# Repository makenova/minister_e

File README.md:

# Minister_E

Minister_e is a hot swap 40% with a centered USB port and the layout of the prime_e V2.
I made this because the designer of the prime_e had no intention of making a hot swap version of the V2 PCB and I wanted one.

The step file can be found in the [docs](./docs) folder.

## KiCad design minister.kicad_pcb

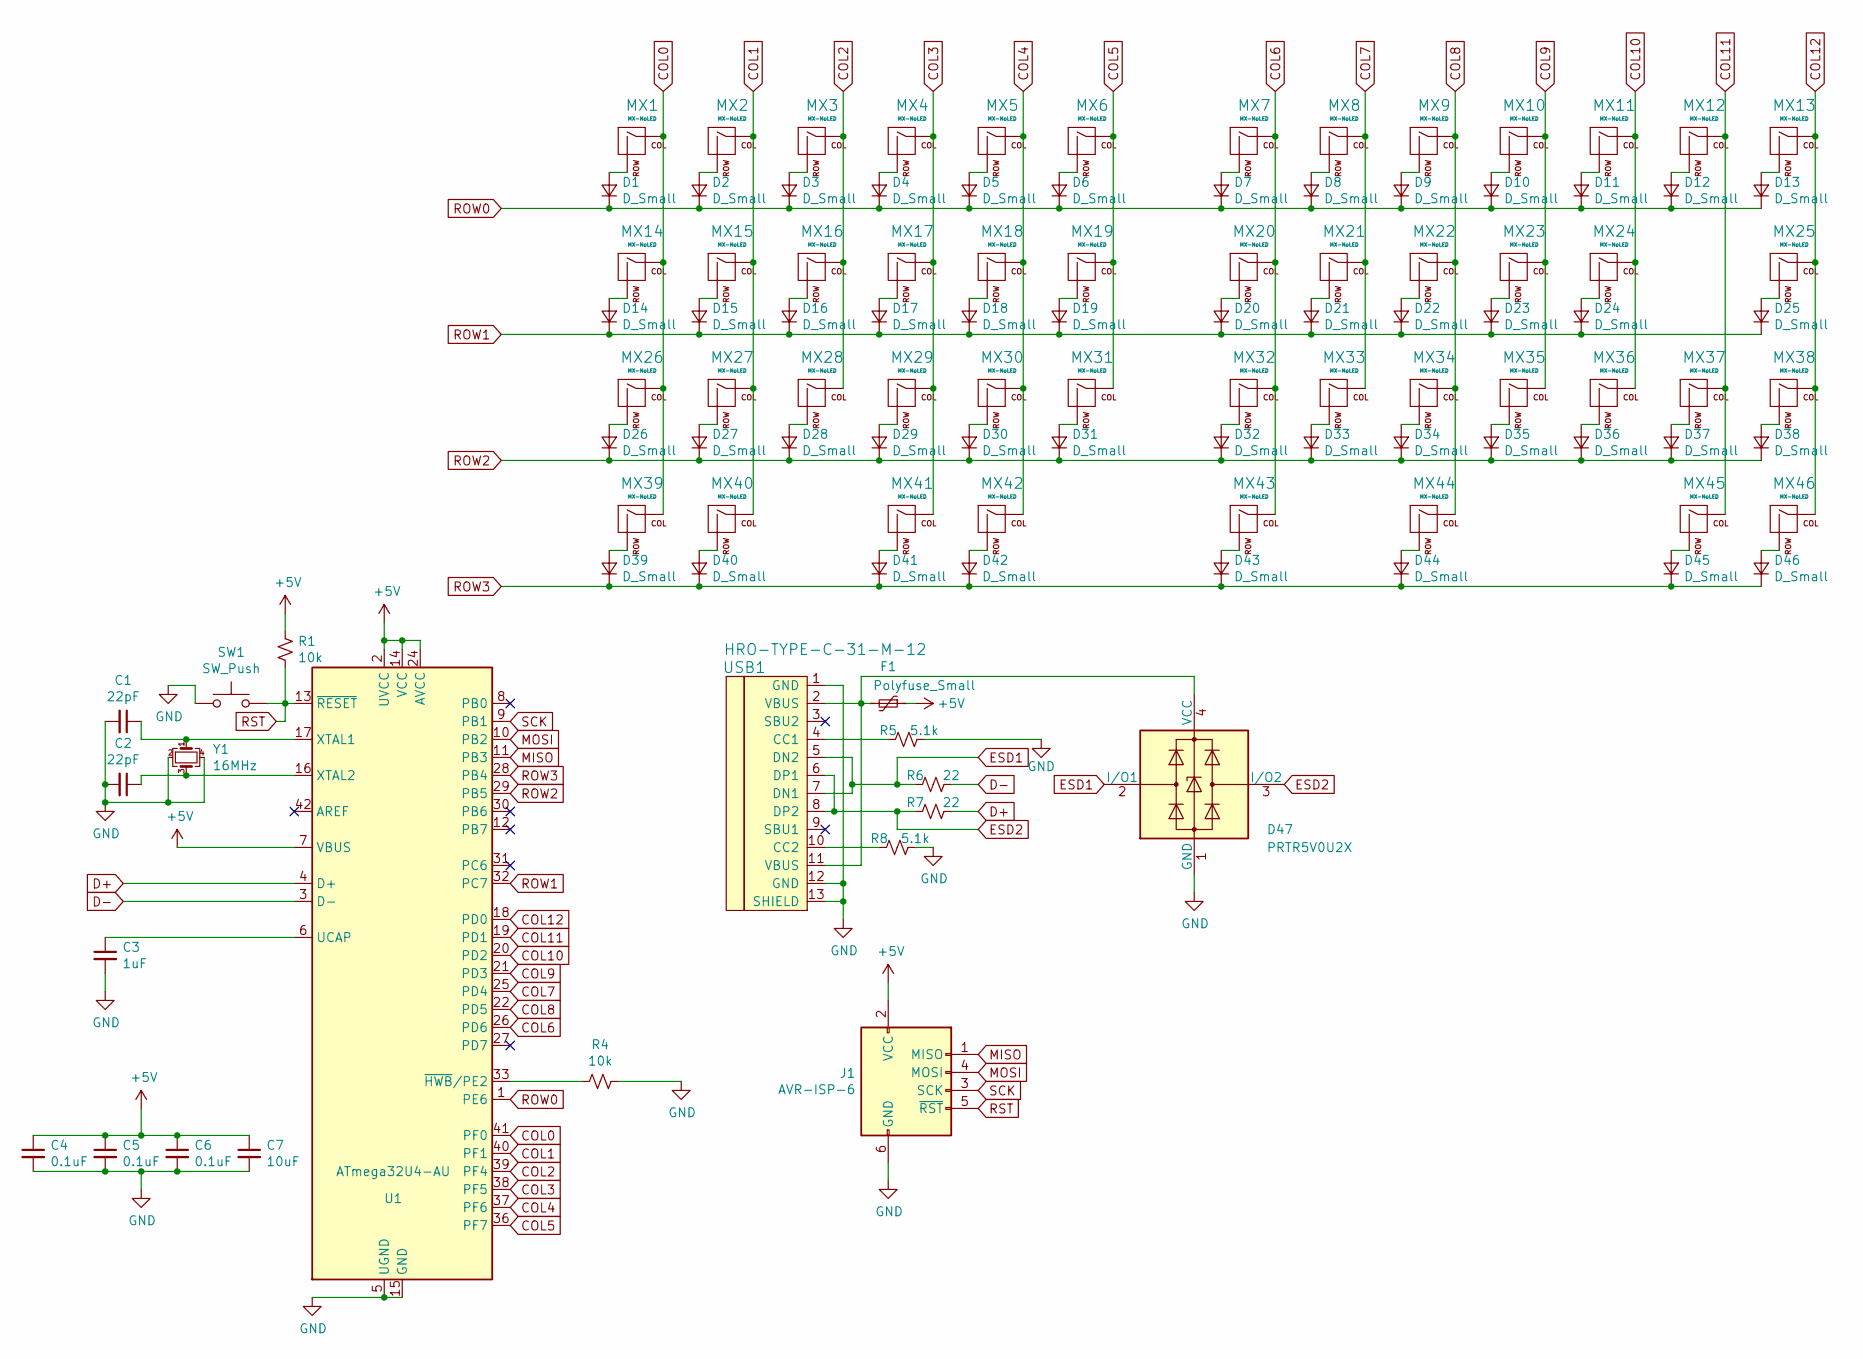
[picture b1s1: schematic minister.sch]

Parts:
C1, C2: 22pF; C_0805_2012Metric
C3: 1uF; C_0805_2012Metric
C4, C5, C6: 0.1uF; C_0805_2012Metric
C7: 10uF; C_0805_2012Metric
D1, D2, D3, D4, D5, D6, D7, D8, D9, D10, D11, D12, D13, D14, D15, D16, D17, D18, D19, D20, D21, D22, D23, D24, D25, D26, D27, D28, D29, D30, D31, D32, D33, D34, D35, D36, D37, D38, D39, D40, D41, D42, D43, D44, D45, D46: D_Small; D_SOD-123
D47: PRTR5V0U2X; SOT-143_Handsoldering
F1: Polyfuse_Small; Fuse_1206_3216Metric
J1: AVR-ISP-6; IDC-Header_2x03_P2.54mm_Vertical
MX1, MX2, MX3, MX4, MX5, MX6, MX7, MX8, MX9, MX10, MX11, MX12, MX13, MX15, MX16, MX17, MX18, MX19, MX20, MX21, MX22, MX23, MX24, MX27, MX28, MX29, MX30, MX31, MX32, MX33, MX34, MX35, MX36, MX37: MX-NoLED; MXOnly-1U-Hotswap
MX14, MX38, MX39, MX40, MX41, MX44, MX45, MX46: MX-NoLED; MXOnly-1.25U-Hotswap
MX25, MX26: MX-NoLED; MXOnly-1.75U-Hotswap
MX42: MX-NoLED; MXOnly-2U-Hotswap-ReversedStabilizers
MX43: MX-NoLED; MXOnly-2.25U-Hotswap-ReversedStabilizers
R1, R4: 10k; R_0805_2012Metric
R5, R8: 5.1k; R_0805_2012Metric
R6, R7: 22; R_0805_2012Metric
SW1: SW_Push; SKQG-1155865
U1: ATmega32U4-AU; TQFP-44_10x10mm_P0.8mm
USB1: HRO-TYPE-C-31-M-12; HRO-TYPE-C-31-M-12-HandSoldering
Y1: 16MHz; Crystal_SMD_3225-4Pin_3.2x2.5mm

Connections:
+5V: C4.1, C5.1, C6.1, C7.1, F1.1, J1.2 (VCC), R1.1, U1.2 (UVCC), U1.7 (VBUS), U1.14 (VCC), U1.24 (AVCC), U1.34 (VCC), U1.44 (AVCC)
COL0: MX1.1 (COL), MX14.1 (COL), MX26.1 (COL), MX39.1 (COL), U1.41 (PF0)
COL1: MX2.1 (COL), MX15.1 (COL), MX27.1 (COL), MX40.1 (COL), U1.40 (PF1)
COL2: MX3.1 (COL), MX16.1 (COL), MX28.1 (COL), U1.39 (PF4)
COL3: MX4.1 (COL), MX17.1 (COL), MX29.1 (COL), MX41.1 (COL), U1.38 (PF5)
COL4: MX5.1 (COL), MX18.1 (COL), MX30.1 (COL), MX42.1 (COL), U1.37 (PF6)
COL5: MX6.1 (COL), MX19.1 (COL), MX31.1 (COL), U1.36 (PF7)
COL6: MX7.1 (COL), MX20.1 (COL), MX32.1 (COL), MX43.1 (COL), U1.26 (PD6)
COL7: MX8.1 (COL), MX21.1 (COL), MX33.1 (COL), U1.25 (PD4)
COL8: MX9.1 (COL), MX22.1 (COL), MX34.1 (COL), MX44.1 (COL), U1.22 (PD5)
COL9: MX10.1 (COL), MX23.1 (COL), MX35.1 (COL), U1.21 (PD3)
COL10: MX11.1 (COL), MX24.1 (COL), MX36.1 (COL), U1.20 (PD2)
COL11: MX12.1 (COL), MX37.1 (COL), MX45.1 (COL), U1.19 (PD1)
COL12: MX13.1 (COL), MX25.1 (COL), MX38.1 (COL), MX46.1 (COL), U1.18 (PD0)
D+: R7.1, U1.4 (D+)
D-: R6.1, U1.3 (D-)
ESD1: D47.2 (I/O1), R6.2, USB1.5 (DN2), USB1.7 (DN1)
ESD2: D47.3 (I/O2), R7.2, USB1.6 (DP1), USB1.8 (DP2)
GND: C1.2, C2.2, C3.2, C4.2, C5.2, C6.2, C7.2, D47.1 (GND), J1.6 (GND), R4.1, R5.1, R8.1, SW1.1, U1.5 (UGND), U1.15 (GND), U1.23 (GND), U1.35 (GND), U1.43 (GND), USB1.1 (GND), USB1.12 (GND), USB1.13 (SHIELD), Y1.2, Y1.4
MISO: J1.1 (MISO), U1.11 (PB3)
MOSI: J1.4 (MOSI), U1.10 (PB2)
unnamed: C1.1, U1.17 (XTAL1), Y1.1
unnamed: C2.1, U1.16 (XTAL2), Y1.3
unnamed: C3.1, U1.6 (UCAP)
unnamed: D1.2 (A), MX1.2 (ROW)
unnamed: D2.2 (A), MX2.2 (ROW)
unnamed: D3.2 (A), MX3.2 (ROW)
unnamed: D4.2 (A), MX4.2 (ROW)
unnamed: D5.2 (A), MX5.2 (ROW)
unnamed: D6.2 (A), MX6.2 (ROW)
unnamed: D7.2 (A), MX7.2 (ROW)
unnamed: D8.2 (A), MX8.2 (ROW)
unnamed: D9.2 (A), MX9.2 (ROW)
unnamed: D10.2 (A), MX10.2 (ROW)
unnamed: D11.2 (A), MX11.2 (ROW)
unnamed: D12.2 (A), MX12.2 (ROW)
unnamed: D13.2 (A), MX13.2 (ROW)
unnamed: D14.2 (A), MX14.2 (ROW)
unnamed: D15.2 (A), MX15.2 (ROW)
unnamed: D16.2 (A), MX16.2 (ROW)
unnamed: D17.2 (A), MX17.2 (ROW)
unnamed: D18.2 (A), MX18.2 (ROW)
unnamed: D19.2 (A), MX19.2 (ROW)
unnamed: D20.2 (A), MX20.2 (ROW)
unnamed: D21.2 (A), MX21.2 (ROW)
unnamed: D22.2 (A), MX22.2 (ROW)
unnamed: D23.2 (A), MX23.2 (ROW)
unnamed: D24.2 (A), MX24.2 (ROW)
unnamed: D25.2 (A), MX25.2 (ROW)
unnamed: D26.2 (A), MX26.2 (ROW)
unnamed: D27.2 (A), MX27.2 (ROW)
unnamed: D28.2 (A), MX28.2 (ROW)
unnamed: D29.2 (A), MX29.2 (ROW)
unnamed: D30.2 (A), MX30.2 (ROW)
unnamed: D31.2 (A), MX31.2 (ROW)
unnamed: D32.2 (A), MX32.2 (ROW)
unnamed: D33.2 (A), MX33.2 (ROW)
unnamed: D34.2 (A), MX34.2 (ROW)
unnamed: D35.2 (A), MX35.2 (ROW)
unnamed: D36.2 (A), MX36.2 (ROW)
unnamed: D37.2 (A), MX37.2 (ROW)
unnamed: D38.2 (A), MX38.2 (ROW)
unnamed: D39.2 (A), MX39.2 (ROW)
unnamed: D40.2 (A), MX40.2 (ROW)
unnamed: D41.2 (A), MX41.2 (ROW)
unnamed: D42.2 (A), MX42.2 (ROW)
unnamed: D43.2 (A), MX43.2 (ROW)
unnamed: D44.2 (A), MX44.2 (ROW)
unnamed: D45.2 (A), MX45.2 (ROW)
unnamed: D46.2 (A), MX46.2 (ROW)
unnamed: D47.4 (VCC), F1.2, USB1.2 (VBUS), USB1.11 (VBUS)
unnamed: R4.2, U1.33 (~HWB~/PE2)
unnamed: R5.2, USB1.4 (CC1)
unnamed: R8.2, USB1.10 (CC2)
ROW0: D1.1 (K), D2.1 (K), D3.1 (K), D4.1 (K), D5.1 (K), D6.1 (K), D7.1 (K), D8.1 (K), D9.1 (K), D10.1 (K), D11.1 (K), D12.1 (K), D13.1 (K), U1.1 (PE6)
ROW1: D14.1 (K), D15.1 (K), D16.1 (K), D17.1 (K), D18.1 (K), D19.1 (K), D20.1 (K), D21.1 (K), D22.1 (K), D23.1 (K), D24.1 (K), D25.1 (K), U1.32 (PC7)
ROW2: D26.1 (K), D27.1 (K), D28.1 (K), D29.1 (K), D30.1 (K), D31.1 (K), D32.1 (K), D33.1 (K), D34.1 (K), D35.1 (K), D36.1 (K), D37.1 (K), D38.1 (K), U1.29 (PB5)
ROW3: D39.1 (K), D40.1 (K), D41.1 (K), D42.1 (K), D43.1 (K), D44.1 (K), D45.1 (K), D46.1 (K), U1.28 (PB4)
RST: J1.5 (~RST), R1.2, SW1.2, U1.13 (~RESET)
SCK: J1.3 (SCK), U1.9 (PB1)

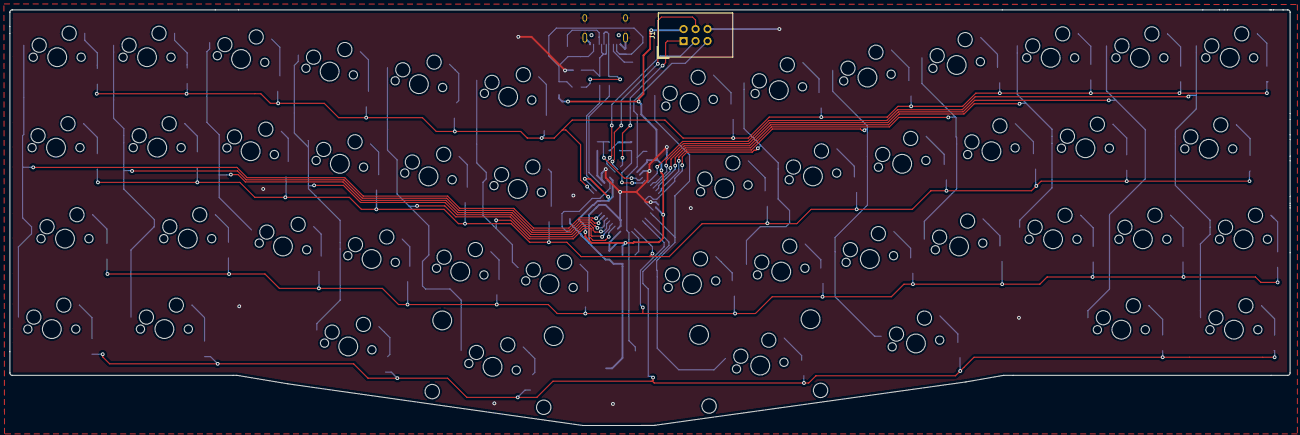
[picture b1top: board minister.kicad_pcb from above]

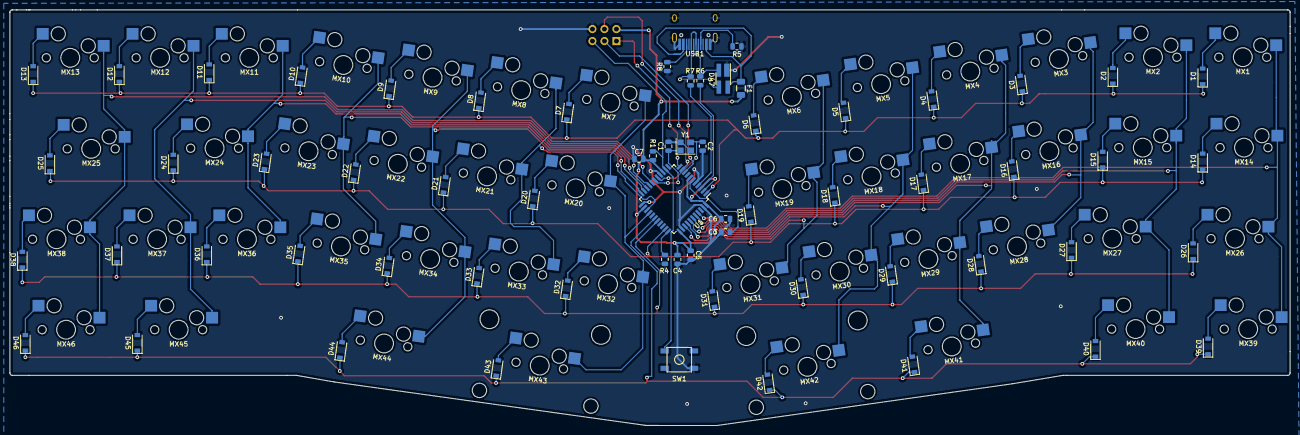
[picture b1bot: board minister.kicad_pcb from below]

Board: 2 copper layers, 271.5 x 88.1 mm, 112 parts (65 on the bottom side), 80 nets.

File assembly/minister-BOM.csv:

"Designator","Quantity","Value","Footprint","LCSC Part #"
"C2, C1, ","2","22pF","0805","C1804"
"C3, ","1","1uF","0805","C28323"
"C4, C5, C6, ","3","0.1uF","0805","C49678"
"C7, ","1","10uF","0805","C15850"
"D20, D7, D43, D32, D21, D8, D33, D22, D9, D44, D34, D23, D10, D35, D24, D11, D36, D12, D45, D37, D25, D13, D46, D38, D30, D42, D5, D18, D29, D41, D4, D17, D28, D3, D16, D27, D40, D2, D15, D26, D39, D1, D14, D31, D6, D19, ","46","D_Small","SOD-123","C81598"
"D47, ","1","PRTR5V0U2X","SOT-143","C78442"
"F1, ","1","Polyfuse_Small","1206","C151162"
"R4, R1, ","2","10k","0805","C17414"
"R5, R8, ","2","5.1k","0805","C27834"
"R6, R7, ","2","22","0805","C17561"
"SW1, ","1","SW_Push","SMD-SW-4_5.1x5.1x1.5","C318884"
"U1, ","1","ATmega32U4-AU","QFP-44_10.0x10.0x0.8P","C44854"
"Y1, ","1","16MHz","SMD-3225_4P","C13738"

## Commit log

2020-04-12 make it so
2020-04-12 add submodules
2020-04-12 add footprint libraries
2020-04-12 create mcu schematic
2020-04-12 schematic complete
2020-04-12 Assign Footprints
2020-04-12 update footprints
2020-04-12 rough component placement on pcb
2020-04-12 move surface mount componets to bottom with 'F'
2020-04-12 rearrange components
2020-04-12 import prime_e edge cuts
2020-04-12 everything laid out
2020-04-12 use shaped edge cuts
2020-04-13 start routing
2020-04-17 more routing
2020-04-18 all routing done? except for gnd
2020-04-19 add ground fill and run drc
2020-04-19 fix drc errors
2020-04-20 replace usb and generate output files
2020-04-20 clean up slik screen
2020-04-20 not sure
2020-05-03 add isp
2020-05-03 clean up and touch up pcb
2020-05-04 submit for production
    generate gerbers and drill files
    generate bom and placement file
    update some parts
2020-05-14 add output of tracespace
2020-05-24 move type c lib to project specific libraries
    generate step file
2020-05-24 add layers image
